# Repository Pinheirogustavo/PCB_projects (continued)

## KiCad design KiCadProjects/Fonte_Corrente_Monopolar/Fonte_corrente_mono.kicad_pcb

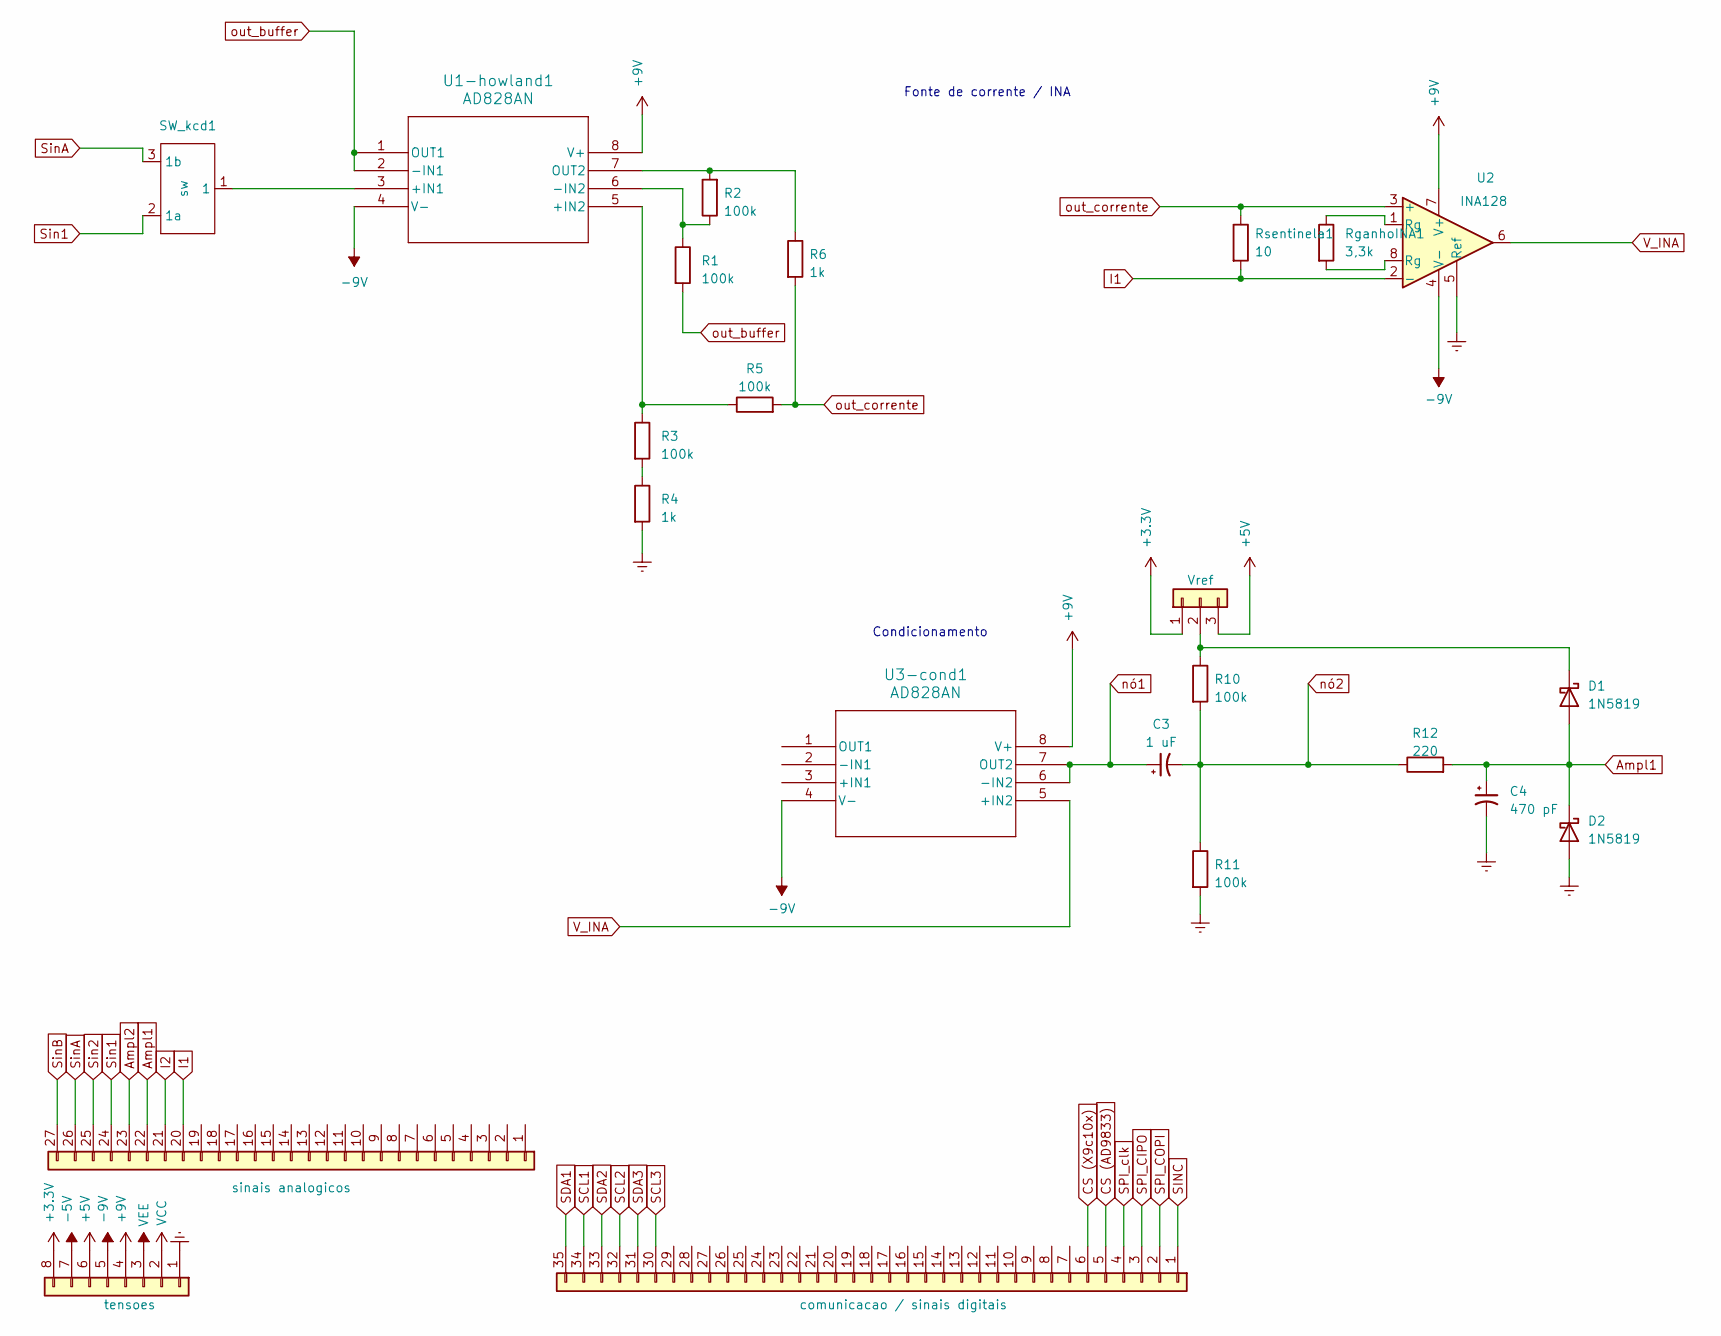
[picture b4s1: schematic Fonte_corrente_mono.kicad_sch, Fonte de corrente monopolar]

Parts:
C3: 1 uF; CP_Radial_D5.0mm_P2.50mm
C4: 470 pF; CP_Radial_D5.0mm_P2.50mm
D1, D2: 1N5819; D_DO-41_SOD81_P10.16mm_Horizontal
J1: Vref; PinHeader_1x03_P2.54mm_Vertical
J2: tensoes; PinSocket_1x08_P2.54mm_Vertical
J3: sinais analogicos; PinSocket_1x27_P2.54mm_Vertical
J4: comunicacao / sinais digitais; PinSocket_1x35_P2.54mm_Vertical
R1, R2, R3, R5, R10, R11: 100k; R_Axial_DIN0207_L6.3mm_D2.5mm_P7.62mm_Horizontal
R4, R6: 1k; R_Axial_DIN0207_L6.3mm_D2.5mm_P7.62mm_Horizontal
R12: 220; R_Axial_DIN0207_L6.3mm_D2.5mm_P7.62mm_Horizontal
RganhoINA1: 3,3k; R_Axial_DIN0207_L6.3mm_D2.5mm_P7.62mm_Horizontal
Rsentinela1: 10; R_Axial_DIN0207_L6.3mm_D2.5mm_P7.62mm_Horizontal
SW_kcd1: sw; chave gangorra 3 pinos
U1-howland1, U3-cond1: AD828AN; N_8_ADI
U2: INA128; DIP-8_W7.62mm

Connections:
+3.3V: J1.1, J2.8
+5V: J1.3, J2.6
+9V: J2.4, U1-howland1.8 (V+), U2.7 (V+), U3-cond1.8 (V+)
-5V: J2.7
-9V: J2.5, U1-howland1.4 (V-), U2.4 (V-), U3-cond1.4 (V-)
Ampl1: C4.1, D1.2 (A), D2.1 (K), J3.22, R12.2
Ampl2: J3.23
CS (AD9833): J4.5
CS (X9c10x): J4.6
Earth: C4.2, D2.2 (A), J2.1, R4.2, R11.2, U2.5 (Ref)
I1: J3.20, Rsentinela1.2, U2.2 (-)
I2: J3.21
unnamed: D1.1 (K), J1.2, R10.1
unnamed: R3.2, R4.1
unnamed: RganhoINA1.1, U2.1 (Rg)
unnamed: RganhoINA1.2, U2.8 (Rg)
unnamed: SW_kcd1.1, U1-howland1.3 (+IN1)
unnamed: R3.1, R5.1, U1-howland1.5 (+IN2)
unnamed: R1.1, R2.1, U1-howland1.6 (-IN2)
unnamed: R2.2, R6.1, U1-howland1.7 (OUT2)
SCL1: J4.34
SCL2: J4.32
SCL3: J4.30
SDA1: J4.35
SDA2: J4.33
SDA3: J4.31
SINC: J4.1
SPI_CIPO: J4.3
SPI_COPI: J4.2
SPI_clk: J4.4
Sin1: J3.24, SW_kcd1.2 (1a)
Sin2: J3.25
SinA: J3.26, SW_kcd1.3 (1b)
SinB: J3.27
VCC: J2.2
VEE: J2.3
V_INA: U2.6, U3-cond1.5 (+IN2)
nó1: C3.1, U3-cond1.6 (-IN2), U3-cond1.7 (OUT2)
nó2: C3.2, R10.2, R11.1, R12.1
out_buffer: R1.2, U1-howland1.1 (OUT1), U1-howland1.2 (-IN1)
out_corrente: R5.2, R6.2, Rsentinela1.1, U2.3 (+)

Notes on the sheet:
Fonte de corrente / INA
Condicionamento

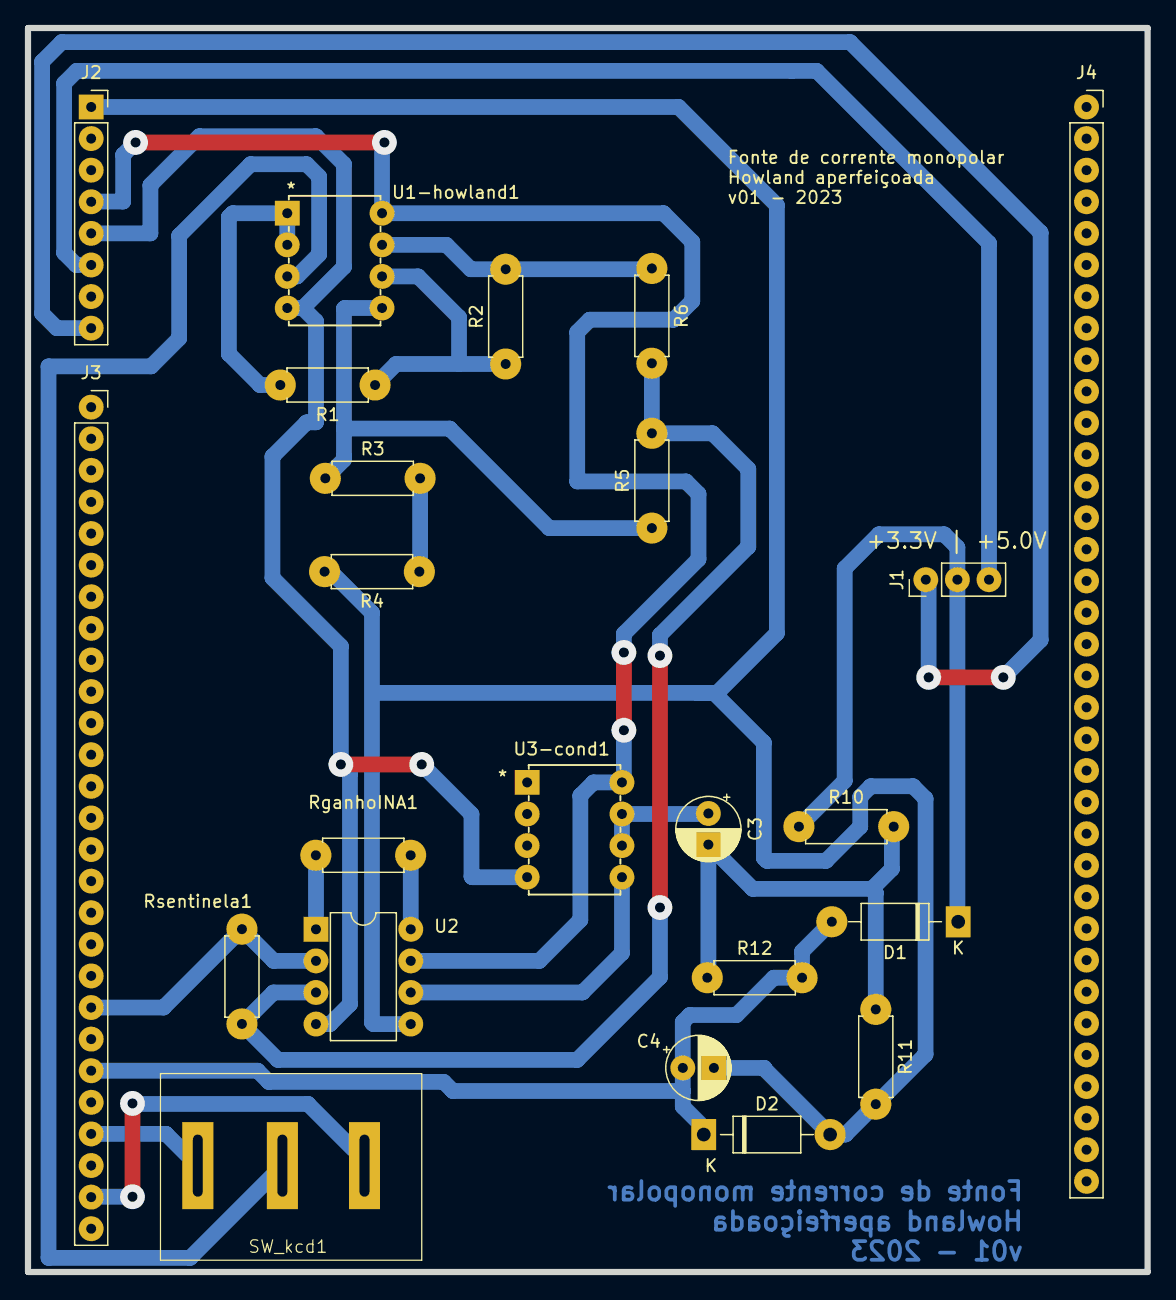
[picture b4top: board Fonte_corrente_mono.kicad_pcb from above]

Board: 2 copper layers, 90.0 x 100.0 mm, 23 parts (0 on the bottom side), 22 nets.

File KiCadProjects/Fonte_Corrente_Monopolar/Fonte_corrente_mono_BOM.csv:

"Id";"Designador";"Footprint";"Quantidade";"Designação";"Fornecedor e referência";
1;"J1";"PinHeader_1x03_P2.54mm_Vertical";1;"Vref";;;
2;"R12";"R_Axial_DIN0207_L6.3mm_D2.5mm_P7.62mm_Horizontal";1;"220";;;
3;"Rsentinela1";"R_Axial_DIN0207_L6.3mm_D2.5mm_P7.62mm_Horizontal";1;"10";;;
4;"C4";"CP_Radial_D5.0mm_P2.50mm";1;"470 pF";;;
5;"U2";"DIP-8_W7.62mm";1;"INA128";;;
6;"J4";"PinSocket_1x35_P2.54mm_Vertical";1;"comunicacao / sinais digitais";;;
7;"U3-cond1,U1-howland1";"N_8_ADI";2;"AD828AN";;;
8;"R10,R1,R2,R11,R3,R5";"R_Axial_DIN0207_L6.3mm_D2.5mm_P7.62mm_Horizontal";6;"100k";;;
9;"J2";"PinSocket_1x08_P2.54mm_Vertical";1;"tensoes";;;
10;"J3";"PinSocket_1x27_P2.54mm_Vertical";1;"sinais analogicos";;;
11;"RganhoINA1";"R_Axial_DIN0207_L6.3mm_D2.5mm_P7.62mm_Horizontal";1;"3,3k";;;
12;"C3";"CP_Radial_D5.0mm_P2.50mm";1;"1 uF";;;
13;"D2,D1";"D_DO-41_SOD81_P10.16mm_Horizontal";2;"1N5819";;;
14;"SW_kcd1";"chave gangorra 3 pinos";1;"sw";;;
15;"R4,R6";"R_Axial_DIN0207_L6.3mm_D2.5mm_P7.62mm_Horizontal";2;"1k";;;

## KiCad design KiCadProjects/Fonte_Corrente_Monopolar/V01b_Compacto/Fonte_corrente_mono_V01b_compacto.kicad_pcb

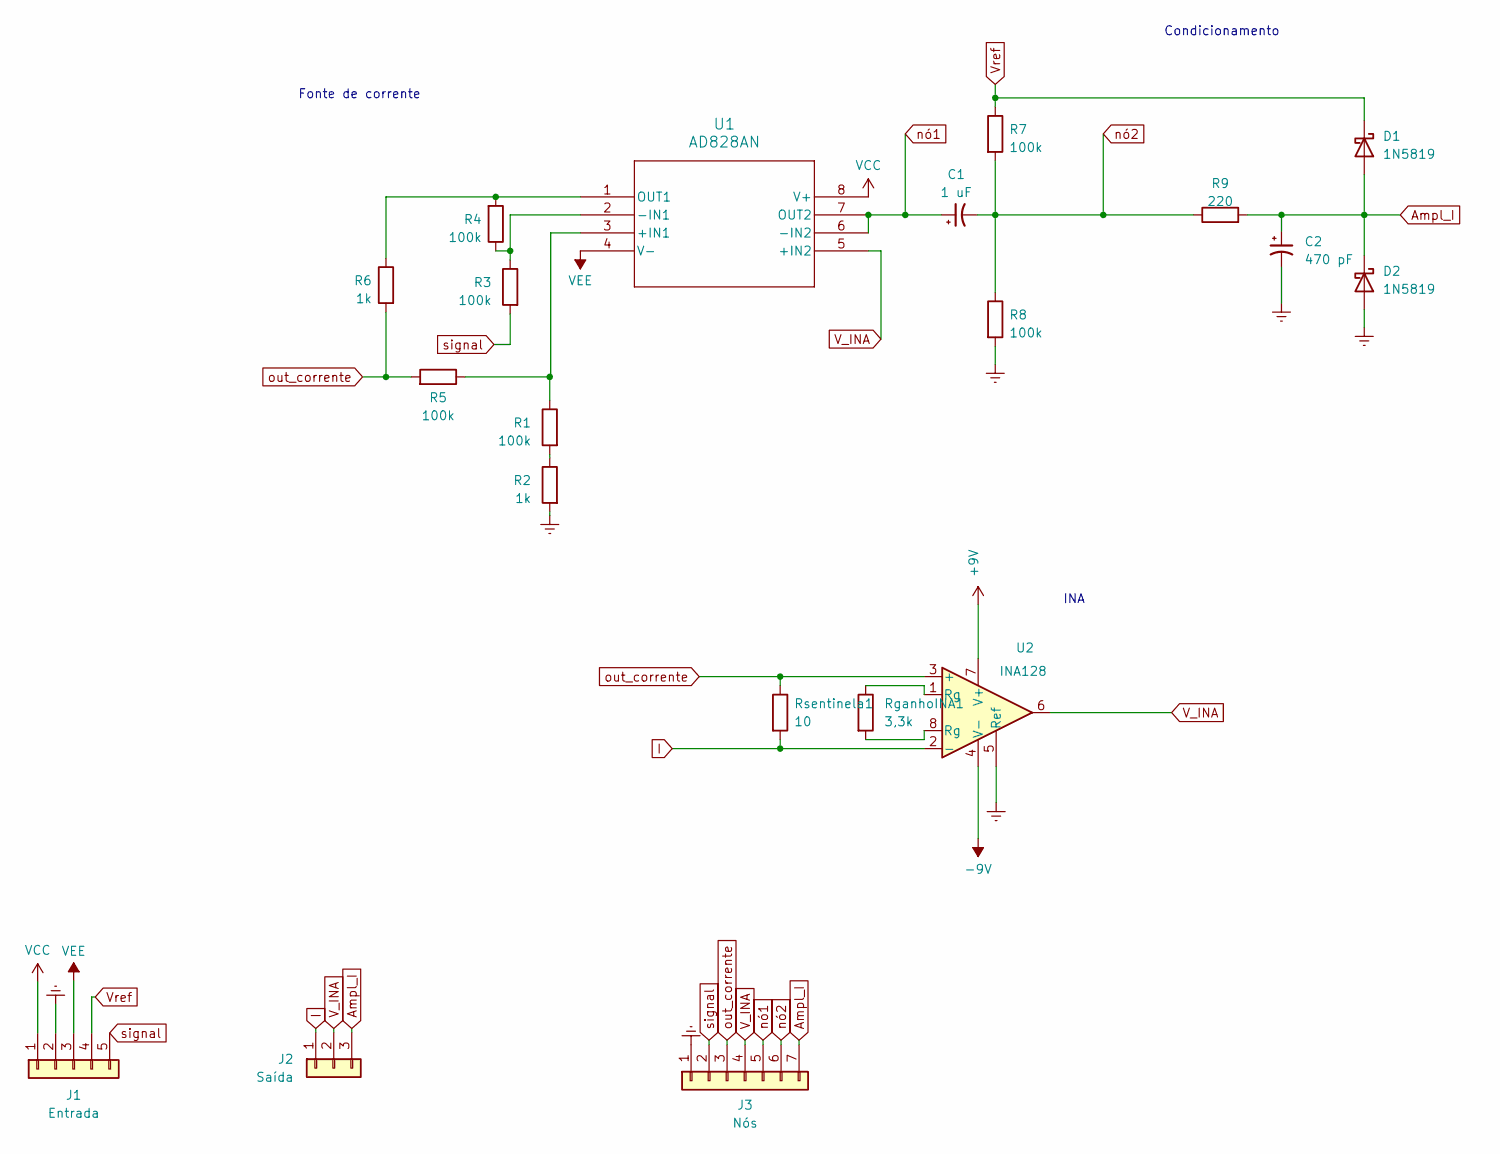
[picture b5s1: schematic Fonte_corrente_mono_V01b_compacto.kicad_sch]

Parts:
C1: 1 uF; CP_Radial_D5.0mm_P2.50mm
C2: 470 pF; CP_Radial_D5.0mm_P2.50mm
D1, D2: 1N5819; D_DO-41_SOD81_P10.16mm_Horizontal
J1: Entrada; PinSocket_1x05_P2.54mm_Vertical
J2: Saída; PinSocket_1x03_P2.54mm_Vertical
J3: Nós; PinHeader_1x07_P2.54mm_Vertical
R1, R3, R4, R5, R7, R8: 100k; R_Axial_DIN0207_L6.3mm_D2.5mm_P7.62mm_Horizontal
R2, R6: 1k; R_Axial_DIN0207_L6.3mm_D2.5mm_P7.62mm_Horizontal
R9: 220; R_Axial_DIN0207_L6.3mm_D2.5mm_P7.62mm_Horizontal
RganhoINA1: 3,3k; R_Axial_DIN0207_L6.3mm_D2.5mm_P7.62mm_Horizontal
Rsentinela1: 10; R_Axial_DIN0207_L6.3mm_D2.5mm_P7.62mm_Horizontal
U1: AD828AN; N_8_ADI
U2: INA128; DIP-8_W7.62mm

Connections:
+9V: U2.7 (V+)
-9V: U2.4 (V-)
Ampl_I: C2.1, D1.2 (A), D2.1 (K), J2.3, J3.7, R9.2
Earth: C2.2, D2.2 (A), J1.2, J3.1, R2.2, R8.2, U2.5 (Ref)
I: J2.1, Rsentinela1.2, U2.2 (-)
unnamed: R1.2, R2.1
unnamed: RganhoINA1.1, U2.1 (Rg)
unnamed: RganhoINA1.2, U2.8 (Rg)
unnamed: R1.1, R5.1, U1.3 (+IN1)
unnamed: R3.1, R4.1, U1.2 (-IN1)
unnamed: R4.2, R6.1, U1.1 (OUT1)
VCC: J1.1, U1.8 (V+)
VEE: J1.3, U1.4 (V-)
V_INA: J2.2, J3.4, U1.5 (+IN2), U2.6
Vref: D1.1 (K), J1.4, R7.1
nó1: C1.1, J3.5, U1.6 (-IN2), U1.7 (OUT2)
nó2: C1.2, J3.6, R7.2, R8.1, R9.1
out_corrente: J3.3, R5.2, R6.2, Rsentinela1.1, U2.3 (+)
signal: J1.5, J3.2, R3.2

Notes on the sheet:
Condicionamento
Fonte de corrente
INA

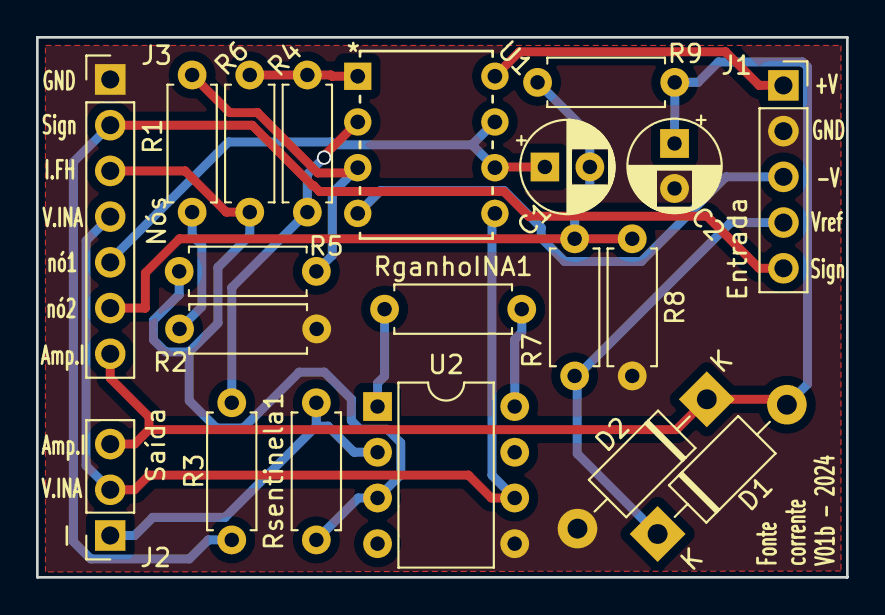
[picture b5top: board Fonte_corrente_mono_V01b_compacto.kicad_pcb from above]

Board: 2 copper layers, 45.0 x 30.0 mm, 20 parts (0 on the bottom side), 17 nets.

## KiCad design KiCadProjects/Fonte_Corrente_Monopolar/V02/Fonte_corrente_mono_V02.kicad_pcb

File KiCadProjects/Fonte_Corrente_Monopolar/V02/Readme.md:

### Os esquemático e visão-3D podem ser conferidos em alta resolução na pasta [print](https://github.com/Pinheirogustavo/PCB_projects/tree/main/KiCadProjects/Fonte_Corrente_Monopolar/V02/print)

## Esquemático

## PCB-3D

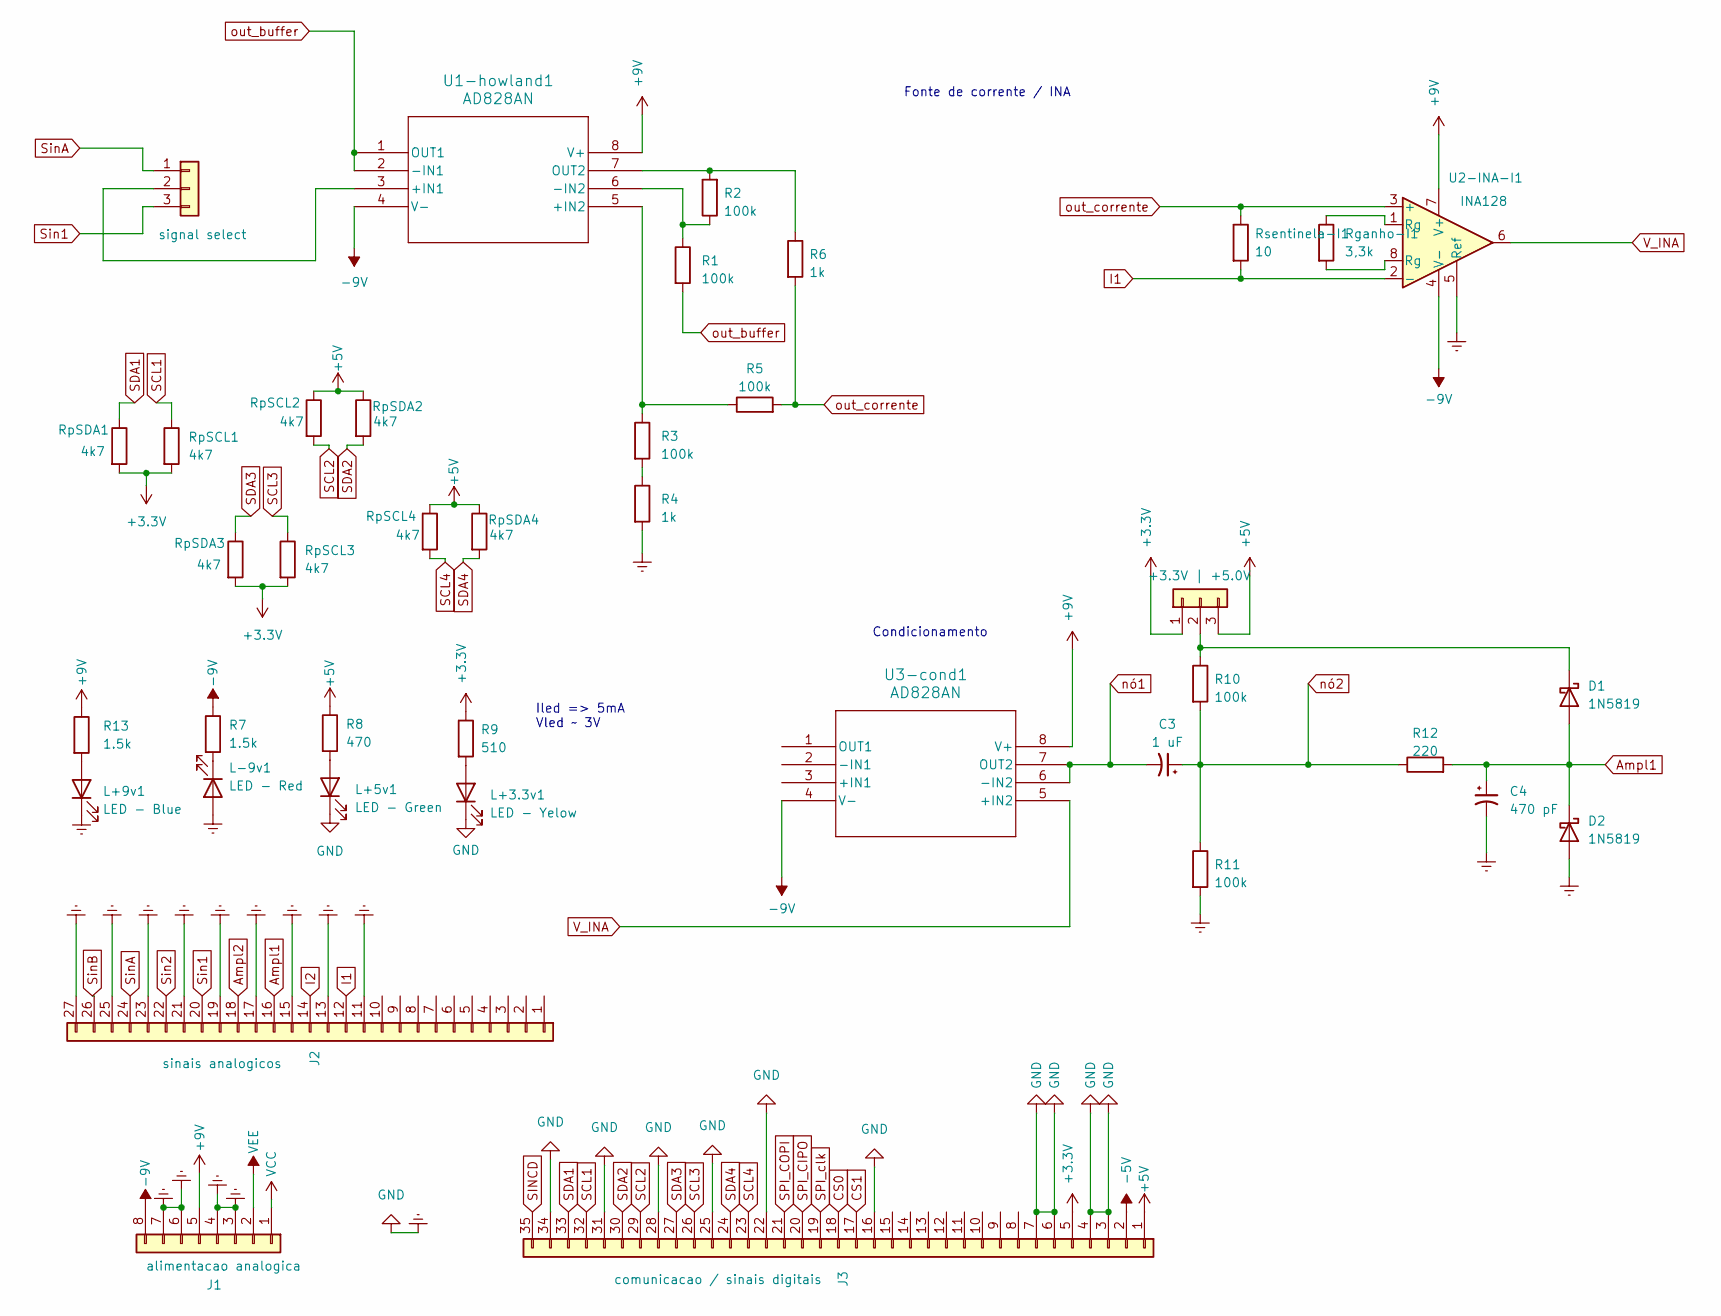
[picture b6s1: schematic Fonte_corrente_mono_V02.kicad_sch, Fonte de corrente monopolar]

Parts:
C3: 1 uF; CP_Radial_D5.0mm_P2.50mm
C4: 470 pF; CP_Radial_D5.0mm_P2.50mm
D1, D2: 1N5819; D_DO-41_SOD81_P10.16mm_Horizontal
J1: alimentacao analogica; PinHeader_1x08_P2.54mm_Vertical
J2: sinais analogicos; PinHeader_1x27_P2.54mm_Vertical
J3: comunicacao / sinais digitais; PinHeader_1x35_P2.54mm_Vertical
J4: signal select; PinHeader_1x03_P2.54mm_Vertical
J7: +3.3V | +5.0V; PinHeader_1x03_P2.54mm_Vertical
L+3.3v1: LED - Yelow; LED_D5.0mm
L+5v1: LED - Green; LED_D5.0mm
L+9v1: LED - Blue; LED_D5.0mm
L-9v1: LED - Red; LED_D5.0mm
R1, R2, R3, R5, R10, R11: 100k; R_Axial_DIN0207_L6.3mm_D2.5mm_P7.62mm_Horizontal
R4, R6: 1k; R_Axial_DIN0207_L6.3mm_D2.5mm_P7.62mm_Horizontal
R7, R13: 1.5k; R_Axial_DIN0207_L6.3mm_D2.5mm_P7.62mm_Horizontal
R8: 470; R_Axial_DIN0207_L6.3mm_D2.5mm_P7.62mm_Horizontal
R9: 510; R_Axial_DIN0207_L6.3mm_D2.5mm_P7.62mm_Horizontal
R12: 220; R_Axial_DIN0207_L6.3mm_D2.5mm_P7.62mm_Horizontal
Rganho-I1: 3,3k; R_Axial_DIN0207_L6.3mm_D2.5mm_P7.62mm_Horizontal
RpSCL1, RpSCL2, RpSCL3, RpSCL4: 4k7; R_Axial_DIN0207_L6.3mm_D2.5mm_P7.62mm_Horizontal
RpSDA1, RpSDA2, RpSDA3, RpSDA4: 4k7; R_Axial_DIN0207_L6.3mm_D2.5mm_P7.62mm_Horizontal
Rsentinela-I1: 10; R_Axial_DIN0207_L6.3mm_D2.5mm_P7.62mm_Horizontal
U1-howland1, U3-cond1: AD828AN; AD828
U2-INA-I1: INA128; DIP-8_W7.62mm

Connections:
+3.3V: J3.5, J7.1, R9.1, RpSCL1.2, RpSCL3.2, RpSDA1.2, RpSDA3.2
+5V: J3.1, J7.3, R8.1, RpSCL2.1, RpSCL4.1, RpSDA2.1, RpSDA4.1
+9V: J1.5, R13.1, U1-howland1.8 (V+), U2-INA-I1.7 (V+), U3-cond1.8 (V+)
-5V: J3.2
-9V: J1.8, R7.1, U1-howland1.4 (V-), U2-INA-I1.4 (V-), U3-cond1.4 (V-)
Ampl1: C4.1, D1.2 (A), D2.1 (K), J2.16, R12.2
Ampl2: J2.18
CS0: J3.18
CS1: J3.17
Earth: C4.2, D2.2 (A), J1.3, J1.4, J1.6, J1.7, J2.11, J2.13, J2.15, J2.17, J2.19, J2.21, J2.23, J2.25, J2.27, J3.3, J3.4, J3.6, J3.7, J3.16, J3.22, J3.25, J3.28, J3.31, J3.34, L+3.3v1.1 (K), L+5v1.1 (K), L+9v1.1 (K), L-9v1.2 (A), R4.2, R11.2, U2-INA-I1.5 (Ref)
I1: J2.12, Rsentinela-I1.2, U2-INA-I1.2 (-)
I2: J2.14
unnamed: D1.1 (K), J7.2, R10.1
unnamed: J4.2, U1-howland1.3 (+IN1)
unnamed: L+3.3v1.2 (A), R9.2
unnamed: L+5v1.2 (A), R8.2
unnamed: L+9v1.2 (A), R13.2
unnamed: L-9v1.1 (K), R7.2
unnamed: R3.2, R4.1
unnamed: Rganho-I1.1, U2-INA-I1.1 (Rg)
unnamed: Rganho-I1.2, U2-INA-I1.8 (Rg)
unnamed: R3.1, R5.1, U1-howland1.5 (+IN2)
unnamed: R1.1, R2.1, U1-howland1.6 (-IN2)
unnamed: R2.2, R6.1, U1-howland1.7 (OUT2)
SCL1: J3.32, RpSCL1.1
SCL2: J3.29, RpSCL2.2
SCL3: J3.26, RpSCL3.1
SCL4: J3.23, RpSCL4.2
SDA1: J3.33, RpSDA1.1
SDA2: J3.30, RpSDA2.2
SDA3: J3.27, RpSDA3.1
SDA4: J3.24, RpSDA4.2
SINCD: J3.35
SPI_CIPO: J3.20
SPI_COPI: J3.21
SPI_clk: J3.19
Sin1: J2.20, J4.3
Sin2: J2.22
SinA: J2.24, J4.1
SinB: J2.26
VCC: J1.1
VEE: J1.2
V_INA: U2-INA-I1.6, U3-cond1.5 (+IN2)
nó1: C3.2, U3-cond1.6 (-IN2), U3-cond1.7 (OUT2)
nó2: C3.1, R10.2, R11.1, R12.1
out_buffer: R1.2, U1-howland1.1 (OUT1), U1-howland1.2 (-IN1)
out_corrente: R5.2, R6.2, Rsentinela-I1.1, U2-INA-I1.3 (+)

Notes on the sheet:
Fonte de corrente / INA
Iled => 5mA Vled ~ 3V
Condicionamento

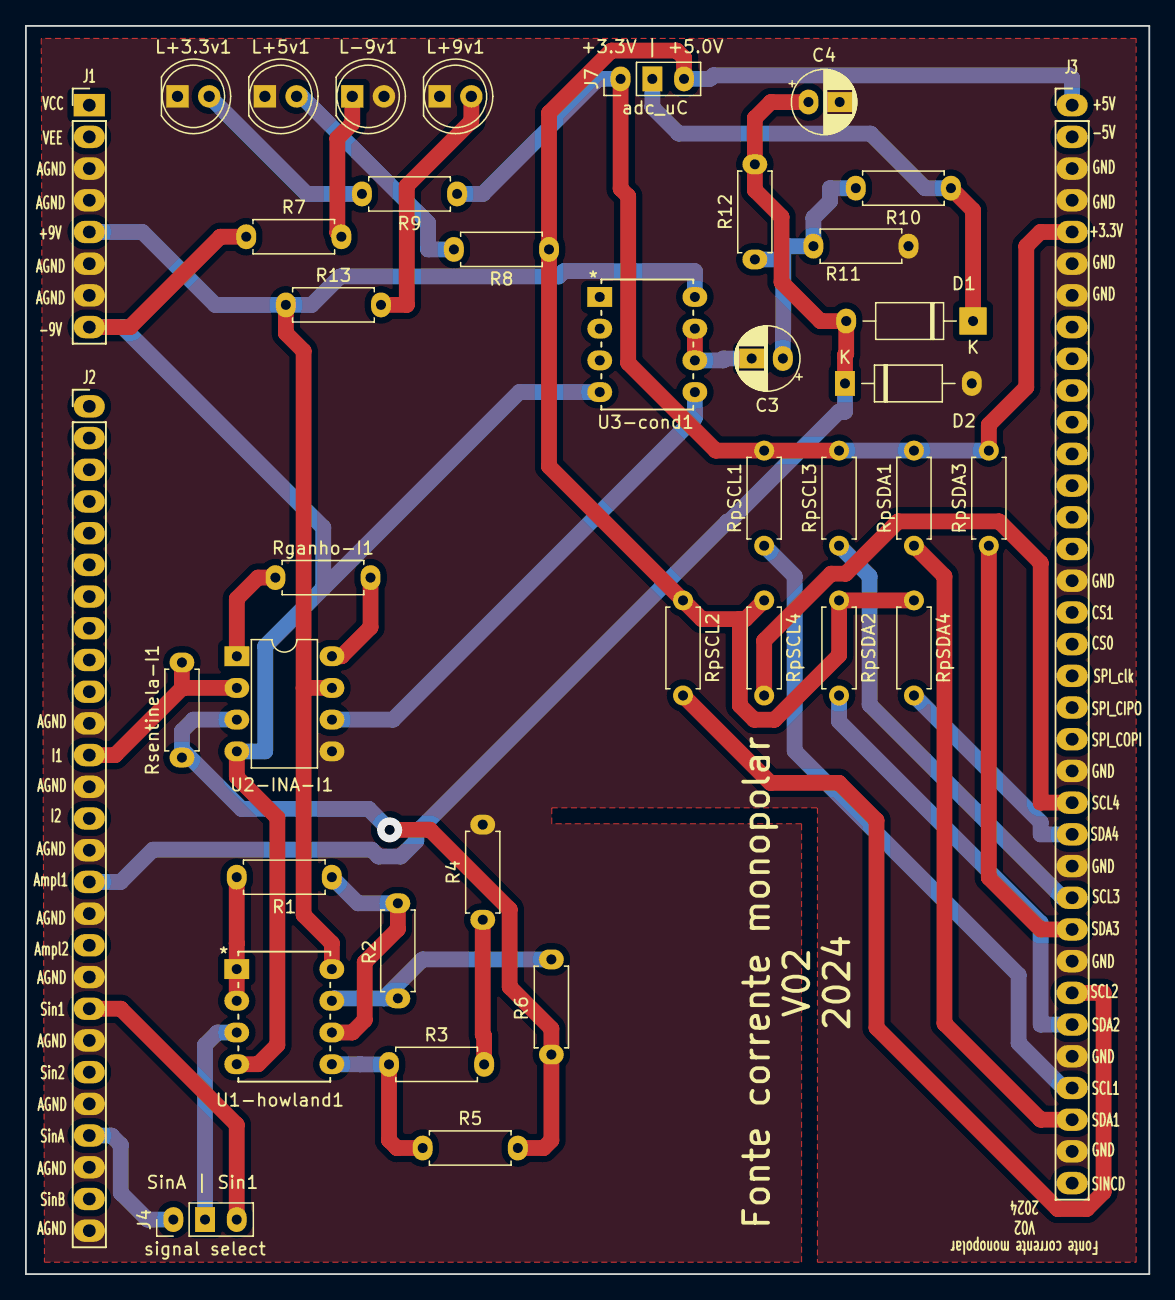
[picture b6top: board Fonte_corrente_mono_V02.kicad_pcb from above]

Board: 2 copper layers, 90.0 x 100.0 mm, 39 parts (0 on the bottom side), 34 nets.

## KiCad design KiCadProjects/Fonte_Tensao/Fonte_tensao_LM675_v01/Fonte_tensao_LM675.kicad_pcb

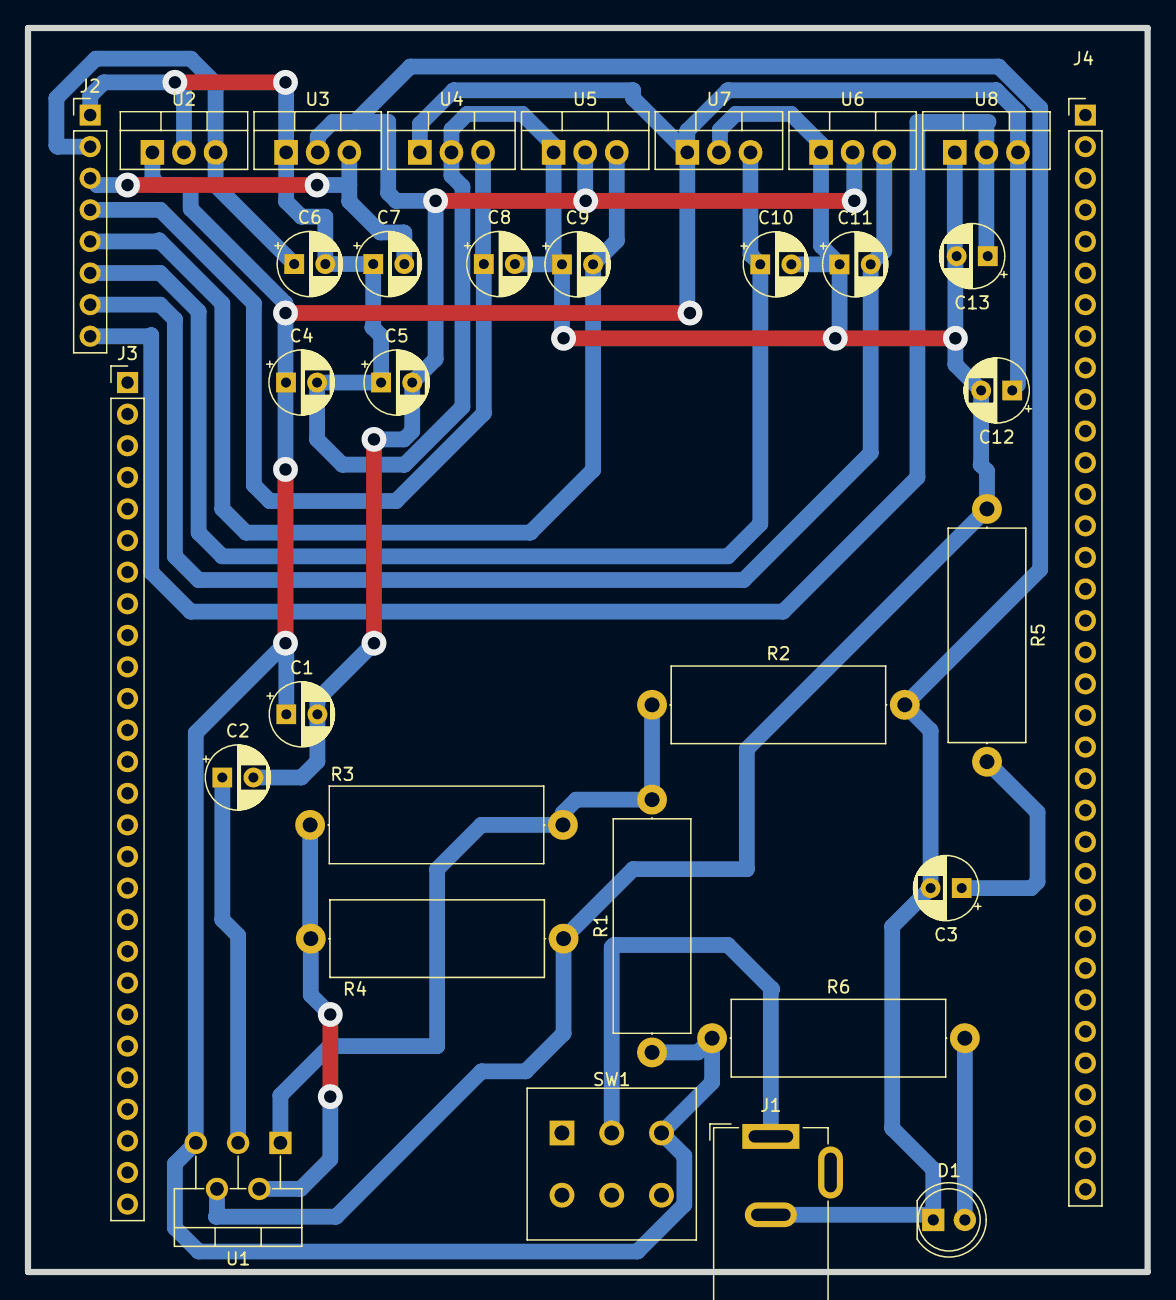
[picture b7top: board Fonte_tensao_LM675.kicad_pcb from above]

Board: 2 copper layers, 90.0 x 100.0 mm, 33 parts (0 on the bottom side), 16 nets.

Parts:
C1: 0.1uf; CP_Radial_D5.0mm_P2.50mm
C2: 0.1uF; CP_Radial_D5.0mm_P2.50mm
C3: 0.22uF; CP_Radial_D5.0mm_P2.50mm
C4: 3.3uF; CP_Radial_D5.0mm_P2.50mm
C5: 22uF; CP_Radial_D5.0mm_P2.50mm
C6, C8, C10: 1uF; CP_Radial_D5.0mm_P2.50mm
C7, C9, C11, C12, C13: 10uF; CP_Radial_D5.0mm_P2.50mm
D1: LED; LED_D5.0mm
J1: Jack; BarrelJack_GCT_DCJ200-10-A_Horizontal
J2: tensoes; PinHeader_1x08_P2.54mm_Vertical
J3: sinais; PinHeader_1x27_P2.54mm_Vertical
J4: comunicacao; PinHeader_1x35_P2.54mm_Vertical
R1, R2: 22k; R_Axial_DIN0617_L17.0mm_D6.0mm_P20.32mm_Horizontal
R3: 1k; R_Axial_DIN0617_L17.0mm_D6.0mm_P20.32mm_Horizontal
R4: 15k; R_Axial_DIN0617_L17.0mm_D6.0mm_P20.32mm_Horizontal
R5: R; R_Axial_DIN0617_L17.0mm_D6.0mm_P20.32mm_Horizontal
R6: 1.5k; R_Axial_DIN0617_L17.0mm_D6.0mm_P20.32mm_Horizontal
SW1: SW_Push_DPDT; SW_PUSH_E-Switch_FS5700DP_DPDT
U1: LM675; TO-220-5_P3.4x3.7mm_StaggerOdd_Lead3.8mm_Vertical
U2: L7812; TO-220-3_Vertical
U3: L7912; TO-220-3_Vertical
U4: L7809; TO-220-3_Vertical
U5: LM7909_TO220; TO-220-3_Vertical
U6: L7905; TO-220-3_Vertical
U7: L7805; TO-220-3_Vertical
U8: LM1117T-3.3; TO-220-3_Vertical

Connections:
+3.3V: C13.1, J2.8, U8.2 (VO)
+5V: C10.1, J2.6, U7.3 (OUT)
+9V: C8.1, J2.4, U4.3 (OUT)
+12V: C6.1, J2.2, U2.3 (OUT)
-5V: C11.2, J2.7, U6.3 (VO)
-9V: C9.2, J2.5, U5.3 (VO)
-12V: C7.2, J2.3, U3.3 (VO)
Earth: C4.2, C5.1, C6.2, C7.1, C8.2, C9.1, C10.2, C11.1, C12.2, C13.2, J2.1, R4.2, R5.1, U1.4, U2.2 (GND), U3.1 (GND), U4.2 (GND), U5.1 (GND), U6.1 (GND), U7.2 (GND), U8.1 (GND)
GND: C1.2, C2.2, C3.2, C5.2, D1.1 (K), J1.2, R2.2, U3.2 (VI), U5.2 (VI), U6.2 (VI)
unnamed: C3.1, R5.2
unnamed: D1.2 (A), R6.2
unnamed: J1.1, SW1.2 (B)
unnamed: R1.2, R2.1, R3.1, U1.1 (+)
unnamed: R3.2, R4.1, U1.2 (-)
unnamed: C2.1, U1.3 (V-)
VCC: C1.1, C4.1, C12.1, R1.1, R6.1, SW1.3 (C), U1.5 (V+), U2.1 (IN), U4.1 (IN), U7.1 (IN), U8.3 (VI)

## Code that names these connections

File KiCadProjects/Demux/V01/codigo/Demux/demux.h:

/*
 * Funções para uso da placa demux "Aquisicao.V01" de 16 canais do tomografo
 * Autor: Gustavo Pinheiro
 */

//Sinais de selecao dos mux que controlam a injecao de corrente
#define A_S0 PB5 //LSB
#define A_S1 PB4
#define A_S2 PB3
#define A_S3 PA15
#define A_S4 PB9 // MSB

//Sinais de selecao dos mux que controlam a drenagem de corrente
#define B_S0 PB15 //LSB
#define B_S1 PB14
#define B_S2 PB13
#define B_S3 PB12
#define B_S4 PB8 // MSB


//Sinais de enable dos mux que controlam a injecao de corrente
#define Enable_A  PA4
#define Enable_A1 PC15
#define Enable_A2 PA0
#define Enable_A3 PA1
#define Enable_A4 PA2

//Sinais de enable dos mux que controlam a drenagem de corrente
#define Enable_B  PA8
#define Enable_B1 PB0
#define Enable_B2 PB1
#define Enable_B3 PB10
#define Enable_B4 PB11


// Funcao que desliga todos os mux's relacionados com a injecao de corrente
void prepara_mux_in(){
  digitalWrite(Enable_A1, HIGH);  // MUX 1  desabilitado
  digitalWrite(Enable_A2, HIGH);  // MUX 2  desabilitado
  digitalWrite(Enable_A3, HIGH);  // MUX 3  desabilitado
  digitalWrite(Enable_A4, HIGH);  // MUX 4  desabilitado
  digitalWrite(Enable_A, LOW);    // MUX 5  habilitado, primeiro da cascata
}

// Funcao que desliga todos os mux's relacionados com a drenagem de corrente
void prepara_mux_out(){
  digitalWrite(Enable_B1, HIGH);  // MUX 1  desabilitado
  digitalWrite(Enable_B2, HIGH);  // MUX 2  desabilitado
  digitalWrite(Enable_B3, HIGH);  // MUX 3  desabilitado
  digitalWrite(Enable_B4, HIGH);  // MUX 4  desabilitado
  digitalWrite(Enable_B, LOW);    // MUX 5 habilitado, primeiro da cascata
}

// Funcao para acionar determinado eletrodo de injecao de corrente
    //A partir do numero desse eletrodo (0-127)
void seleciona_canal_in(int canal){
  prepara_mux_in();
  //canais iniciam no num 0
  byte A = bitRead(canal,0); //LSB canal
  byte B = bitRead(canal,1);
  byte C = bitRead(canal,2);
  byte D = bitRead(canal,3);
  byte E = bitRead(canal,4); //MSB canal

  Serial.print("canal ");
  Serial.println(canal);
  Serial.print(A);
  Serial.print(B);
  Serial.print(C);
  Serial.print(D);
  Serial.println(E);

  digitalWrite(A_S0, A); // B5
  digitalWrite(A_S1, B); // B4
  digitalWrite(A_S2, C); // B3
  digitalWrite(A_S3, D); // A15
  digitalWrite(A_S4, E); // B9

  if (canal<8){ // liga apenas o mux A1
      digitalWrite(Enable_A1,0);
  } else if(canal<16){ //liga apenas o mux A2
      digitalWrite(Enable_A2,0);
  } else if(canal<24){ //liga apenas o mux A3
      digitalWrite(Enable_A3,0);
  } else if(canal<32){ //liga apenas o mux A4
      digitalWrite(Enable_A4,0);
  }
}

// Funcao para acionar determinado eletrodo de drenagem de corrente
    //A partir do numero desse eletrodo (128-255)
void seleciona_canal_out(int canal){
  prepara_mux_out();
  //canais iniciam no num 0
  int A = bitRead(canal,0); //LSB canal
  int B = bitRead(canal,1);
  int C = bitRead(canal,2);
  int D = bitRead(canal,3);
  int E = bitRead(canal,4); //MSB canal

  Serial.print("canal ");
  Serial.println(canal);
  Serial.print(A);
  Serial.print(B);
  Serial.print(C);
  Serial.print(D);
  Serial.println(E);

  digitalWrite(B_S0, A);
  digitalWrite(B_S1, B);
  digitalWrite(B_S2, C);
  digitalWrite(B_S3, D);
  digitalWrite(B_S4, E);

  if (canal<8){ //liga apenas o mux B1
      digitalWrite(Enable_B1,0);
    } else if(canal<16){ //liga apenas o mux B2
      digitalWrite(Enable_B2,0);
    } else if(canal<24){ //liga apenas o mux B3
      digitalWrite(Enable_B3,0);
    } else if(canal<32){ //liga apenas o mux B4
      digitalWrite(Enable_B,0);
    }
}

//Funcao define a GPIO do uC relacionada com controle do mux
void configura_pinos_mux(){
  // Variaveis de seleção do Mux
  //IN current
  pinMode(A_S0, OUTPUT);
  pinMode(A_S1, OUTPUT);
  pinMode(A_S2, OUTPUT);
  pinMode(A_S3, OUTPUT);
  pinMode(A_S4, OUTPUT);
  //OUT current
  pinMode(B_S0, OUTPUT);
  pinMode(B_S1, OUTPUT);
  pinMode(B_S2, OUTPUT);
  pinMode(B_S3, OUTPUT);
  pinMode(B_S4, OUTPUT);

  //  Variaveis de Habilitação do MUX IN (Nivel logico baixo)
  pinMode(Enable_A1, OUTPUT); //  MUX 1 "Eletrodo 0 a 7"
  pinMode(Enable_A2, OUTPUT); //  MUX 2 "Eletrodo 8 a 15"
  pinMode(Enable_A3, OUTPUT); //  MUX 3 "Eletrodo 16 a 23"
  pinMode(Enable_A4, OUTPUT); //  MUX 4 "Eletrodo 24 a 31"
  pinMode(Enable_A, OUTPUT);  //  MUX 5  primeiro da cascata
  //  Variaveis de Habilitação do MUX OUT (Nivel logico baixo)
  pinMode(Enable_B1, OUTPUT); //  MUX 1 "Eletrodo 0 a 7"
  pinMode(Enable_B2, OUTPUT); //  MUX 2 "Eletrodo 8 a 15"
  pinMode(Enable_B3, OUTPUT); //  MUX 3 "Eletrodo 16 a 23"
  pinMode(Enable_B4, OUTPUT); //  MUX 4 "Eletrodo 24 a 31"
  pinMode(Enable_B, OUTPUT);  //  MUX 5  primeiro da cascata
}
